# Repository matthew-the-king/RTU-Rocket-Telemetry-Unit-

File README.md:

# RTU-Rocket-Telemetry-Unit-
The RTU(Rocket Telemetry Unit) is an all-in-one solution for logging and transmitting data, plus controlling up to 3 servos. 

## Specifications
The RTU contains the following:<br>
MCU: STM32H725RGV6<br>
Barometer: BMP581<br>
IMU: BMI270<br>

For Power, the RTU has a 3.3V regulator and a 5v regulator for servos.<br>

## Recording Data
The RTU can record data to an SD card, provided that an SD card is inserted into the SD card port.<br>

## Transmitting Data
The RTU can transmit data through an on-board LoRa module; you must connect the appropriate u.fl antenna to the antenna port for the module to transmit.<br>

## Servo Control
The RTU can control up to three 5V servos; the servo ports can be found in these locations:<br>

## Production 
|Designator                                                                                      |Footprint                               |Quantity|Value                  |    Link   | Price |
|------------------------------------------------------------------------------------------------|----------------------------------------|--------|-----------------------|-----------|-------|
|C10, C12, C19, C28, C36, C40                                                                    |0603                                    |6       |1uF                    | [Link](https://www.digikey.com/en/products/detail/kemet/C0603C105K4RACTU/2199788) | $0.83(Cheaper to buy 10) | 
|C11, C29, C30, C37, C38, C39                                                                    |0603                                    |6       |10uF                   | [Link](https://www.digikey.com/en/products/detail/murata-electronics/GRT188R61C106KE13D/5416739) | $1.75(Cheaper to buy 10)|
|C13, C14, C15, C16, C17, C18, C21, C22, C27, C3, C32, C34, C35, C4, C42, C43, C5, C6, C7, C8, C9|0402                                    |21      |0.1uF                  | [Link](https://www.digikey.com/en/products/detail/murata-electronics/GCM155R71H104KE02D/4903704) | $0.74 |
|C2, C49, C50                                                                                    |0603                                    |3       |22uF                   | [Link](https://www.digikey.com/en/products/detail/samsung-electro-mechanics/CL10A226MO7JZNC/7320581) | $2.40 |
|C20, C31, C41, C46, C47, C48                                                                    |CAP_E61_CHC                             |6       |100uF                  | [Link](https://www.digikey.com/en/products/detail/chemi-con/APXG160ARA101ME61G/3983370) | $4.26 |
|C23, C24                                                                                        |0603                                    |2       |2.2uF                  | [Link](https://www.digikey.com/en/products/detail/murata-electronics/GRM188R71A225KE15D/1033256) | $0.32 |
|C25, C26                                                                                        |0402                                    |2       |10pF                   | [Link](https://www.digikey.com/en/products/detail/murata-electronics/GRM1555C1H100FA01D/2543854) | $0.20 |
|C33                                                                                             |0603                                    |1       |4.7uF                  | [Link](https://www.digikey.com/en/products/detail/murata-electronics/GRM188R61E475KE11D/3900465) | $0.26 |
|C44                                                                                             |0603                                    |1       |4700pF                 | [Link](https://www.digikey.com/en/products/detail/murata-electronics/GRM1885C1H472JA01D/4421616) | $0.12 | 
|C45                                                                                             |0402                                    |1       |100pF                  | [Link](https://www.digikey.com/en/products/detail/murata-electronics/GRM1555C1H101GA01D/3693920) | $0.11 |
|D1                                                                                              |0805                                    |1       |LED                    | [Link](https://www.digikey.com/en/products/detail/liteon/LTST-C170GKT/269226?s=N4IgTCBcDaIDIBUDKCC0BhAjAdgAwHEBpBEAXQF8g) | $0.17 |
|FB1                                                                                             |0603                                    |1       |120R                   | [Link](https://www.digikey.com/en/products/detail/pulse-electronics/PE-0603PFB121ST/5050544) | $0.10 |
|FPWM1, PFM1, R15, R16, R6, R7                                                                   |0402                                    |6       |10kΩ                   | [Link](https://www.digikey.com/en/products/detail/yageo/RC0402JR-0710KL/726418?s=N4IgTCBcDaIEoGEAMAWJYBScC0SDsAjEgNIAyIAugL5A) | $0.21(Cheaper to buy 10) |
|J1                                                                                              |GCT_MEM2075-00-140-01-A                 |1       |MEM2075-00-140-01-A    | [Link](https://www.digikey.com/en/products/detail/gct/MEM2075-00-140-01-A/9859614) | $1.92 |
|J2                                                                                              |SAMESKY_UJ20-C-H-G-SMT-P16-TR           |1       |UJ20-C-H-G-SMT-1-P16-TR| [Link](https://www.digikey.com/en/products/detail/same-sky-formerly-cui-devices/UJ20-C-H-G-SMT-P16-TR/24818595) | $0.65 |
|J4                                                                                              |JST_B6B-XH-A                            |1       |B6B-XH-A               | [Link](https://www.digikey.com/en/products/detail/jst-sales-america-inc/B6B-XH-A/1000381) | $0.23 |
|J5                                                                                              |JST_B4B-XH-A                            |1       |B4B-XH-A               | [Link](https://www.digikey.com/en/products/detail/jst-sales-america-inc/B4B-XH-A/1651047) | $0.17 |
|L1                                                                                              |1008                                    |1       |1uH                    | [Link](https://www.digikey.com/en/products/detail/murata-electronics/DFE252012P-1R0M-P2/5247258?s=N4IgTCBcDaICIDECiYCsYAMBGMAFAtFgEoYCyAvLmAAQgC6AvkA) | $0.22 |
|L2                                                                                              |L_Wurth_WE-LHCA-1040                    |1       |4.7uH                  | [Link](https://www.digikey.com/en/products/detail/w%C3%BCrth-elektronik/784373680047/24774011) | $3.35 |
|R1, R2                                                                                          |0402                                    |2       |5.1kΩ                  | [Link](https://www.digikey.com/en/products/detail/yageo/RC0402FR-075K1L/726624?s=N4IgTCBcDaIEoGEAMAWJYBicC0SDsArANICMAMiALoC%2BQA) | $0.20 |
|R10                                                                                             |0402                                    |1       |330Ω                   | [Link](https://www.digikey.com/en/products/detail/yageo/RC0402FR-07330RL/726594) | $0.10 |
|R11, R12, R4, R5                                                                                |0402                                    |4       |4.7kΩ                  | [Link](https://www.digikey.com/en/products/detail/yageo/RC0402JR-074K7L/726477) | $0.21(Cheaper to buy 10) |
|R13                                                                                             |0402                                    |1       |27.4kΩ                 | [Link](https://www.digikey.com/en/products/detail/yageo/RC0402FR-0727K4L/2827587) | $0.10 |
|R14                                                                                             |0402                                    |1       |23.2kΩ                 | [Link](https://www.digikey.com/en/products/detail/panasonic-industry/ERJ-2RKF2322X/192235) | $0.10 |
|R3                                                                                              |0402                                    |1       |0Ω                     | [Link](https://www.digikey.com/en/products/detail/panasonic-industry/ERJ-2GE0R00X/146727) | $0.10 |
|R8                                                                                              |0603                                    |1       |511kΩ                  | [Link](https://www.digikey.com/en/products/detail/yageo/RC0603FR-07511KL/727288) | $0.10 |
|R9                                                                                              |0603                                    |1       |91kΩ                   | [Link](https://www.digikey.com/en/products/detail/yageo/RC0603JR-0791KL/726841) | $0.10 |
|U1                                                                                              |QFN-68-1EP_8x8mm_P0.4mm_EP6.4x6.4mm     |1       |STM32H725RGVx          | [Link](https://www.digikey.com/en/products/detail/stmicroelectronics/STM32H725RGV6/18085383) | $14.22 |
|U2                                                                                              |QFN10_BMP581_BOS                        |1       |BMP581                 | [Link](https://www.digikey.com/en/products/detail/bosch-sensortec/BMP581/16036134) | $3.35 |
|U3                                                                                              |XDCR_BMI270                             |1       |BMI270                 | [Link](https://www.digikey.com/en/products/detail/bosch-sensortec/BMI270/9974486) | $4.23 |
|U4                                                                                              |COMM-SMD_12P-L11.6-W11.0-P1.27_114993390|1       |WIO-SX1262_C9900174795 | [Link](https://www.digikey.com/en/products/detail/seeed-technology-co-ltd/114993390/25835823) | $5.95 |
|U5                                                                                              |PSON50P145X100X60-6N                    |1       |TPD4S012DRYR           | [Link](https://www.digikey.com/en/products/detail/texas-instruments/TPD4S012DRYR/2037539) | $1.19 |
|U6                                                                                              |VAL0015A-MFG                            |1       |XTPS55285VALR          | [Link](https://www.digikey.com/en/products/detail/texas-instruments/TPS55285VALR/28143335) | $4.15 |
|U7                                                                                              |SOT50P160X60-8N                         |1       |TPS631000DRLR          | [Link](https://www.digikey.com/en/products/detail/texas-instruments/TPS631000DRLR/15965499) | $2.20 |
|Y1                                                                                              |CRYSTAL_ABM8G_ABR                       |1       |ABM8G-25.000MHZ-B4Y-T  | [Link](https://www.digikey.com/en/products/detail/abracon-llc/ABM8G-25-000MHZ-B4Y-T/2218043) | $0.86 |
||||||Total Price:$54.96 + plus shipping ~ $5.00|

For the PCB, I recommend using JLPCB; it costs only $8 for 5 boards plus shipping. 
## Firmware
Currently, there is no firmware because I do not have the board yet.

# Important Information
To ensure that the 3.3V regulator works correctly, make sure to place only ONE of the resistors circled; it is recommended to place the FPWM resistor and not the PFM resistor.<br>

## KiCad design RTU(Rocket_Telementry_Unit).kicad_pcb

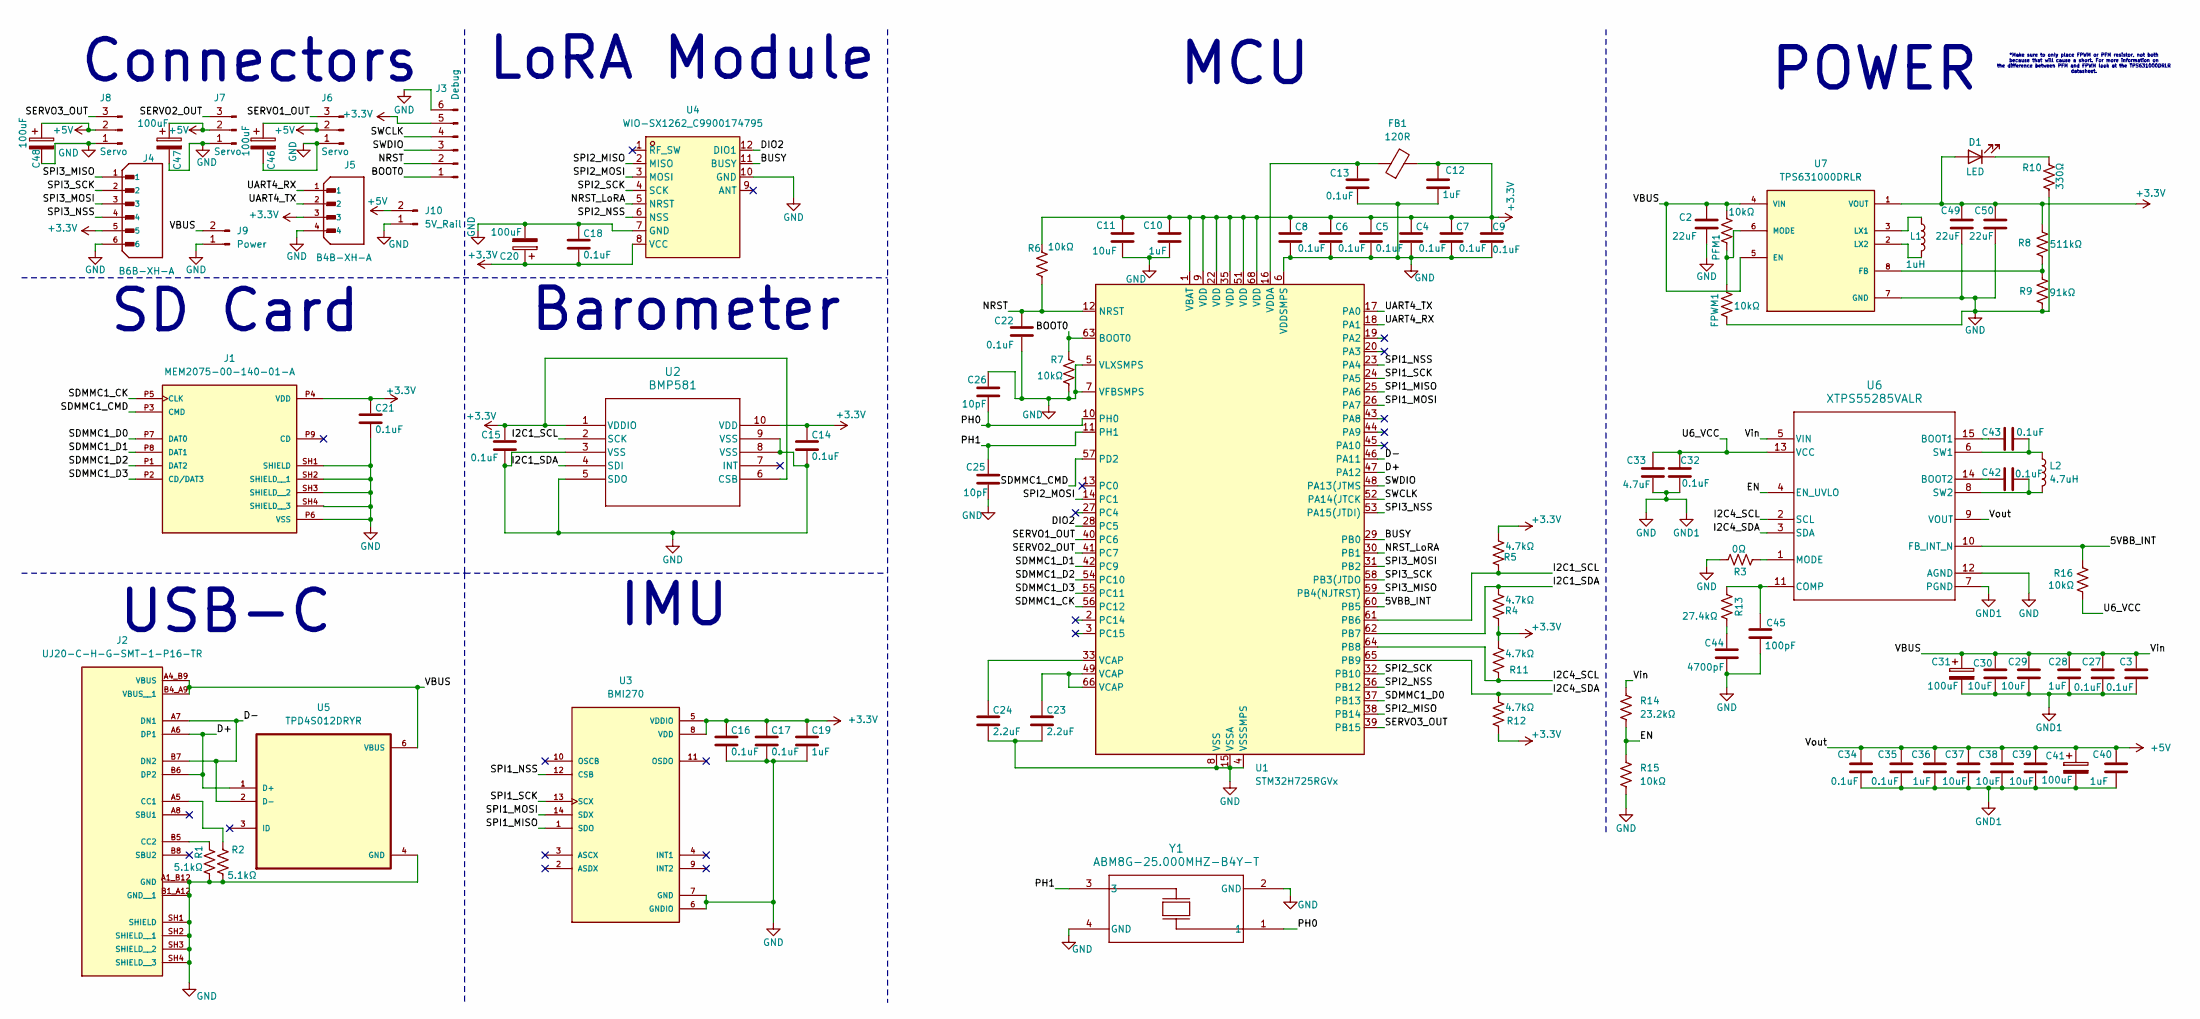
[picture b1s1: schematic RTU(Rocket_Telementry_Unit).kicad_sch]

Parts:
C2, C49, C50: 22uF; C_0603_1608Metric
C3, C4, C5, C6, C7, C8, C9, C13, C14, C15, C16, C17, C18, C21, C22, C27, C32, C34, C35, C42, C43: 0.1uF; C_0402_1005Metric
C10, C12, C19, C28, C36, C40: 1uF; C_0603_1608Metric
C11, C29, C30, C37, C38, C39: 10uF; C_0603_1608Metric
C20, C31, C41, C46, C47, C48: 100uF; CAP_E61_CHC
C23, C24: 2.2uF; C_0603_1608Metric
C25, C26: 10pF; C_0402_1005Metric
C33: 4.7uF; C_0603_1608Metric
C44: 4700pF; C_0603_1608Metric
C45: 100pF; C_0402_1005Metric
D1: LED; LED_0805_2012Metric
FB1: 120R; L_0603_1608Metric
FPWM1: 10kΩ; R_0402_1005Metric
J1: MEM2075-00-140-01-A; GCT_MEM2075-00-140-01-A; PARTREV A
J2: UJ20-C-H-G-SMT-1-P16-TR; SAMESKY_UJ20-C-H-G-SMT-P16-TR; PARTREV 1.0
J3: Debug; PinHeader_1x06_P2.54mm_Vertical
J4: B6B-XH-A; JST_B6B-XH-A; PARTREV 7/4/21
J5: B4B-XH-A; JST_B4B-XH-A; PARTREV 7/4/21
J6, J7, J8: Servo; PinHeader_1x03_P2.54mm_Vertical
J9: Power; PinHeader_1x02_P2.54mm_Vertical
J10: 5V_Rail; PinHeader_1x02_P2.54mm_Vertical
L1: 1uH; L_1008_2520Metric
L2: 4.7uH; L_Wurth_WE-LHCA-1040
PFM1: 10kΩ; R_0402_1005Metric
R1, R2: 5.1kΩ; R_0402_1005Metric
R3: 0Ω; R_0402_1005Metric
R4, R5, R11, R12: 4.7kΩ; R_0402_1005Metric
R6, R7, R15, R16: 10kΩ; R_0402_1005Metric
R8: 511kΩ; R_0603_1608Metric
R9: 91kΩ; R_0603_1608Metric
R10: 330Ω; R_0402_1005Metric
R13: 27.4kΩ; R_0402_1005Metric
R14: 23.2kΩ; R_0402_1005Metric
U1: STM32H725RGVx; QFN-68-1EP_8x8mm_P0.4mm_EP6.4x6.4mm
U2: BMP581; QFN10_BMP581_BOS
U3: BMI270; XDCR_BMI270
U4: WIO-SX1262_C9900174795; COMM-SMD_12P-L11.6-W11.0-P1.27_114993390; MPN Wio-SX1262; LCSC Part C9900174795
U5: TPD4S012DRYR; PSON50P145X100X60-6N
U6: XTPS55285VALR; VAL0015A-MFG
U7: TPS631000DRLR; SOT50P160X60-8N; PARTREV B
Y1: ABM8G-25.000MHZ-B4Y-T; CRYSTAL_ABM8G_ABR

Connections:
+3.3V: C4.1, C5.1, C6.1, C7.1, C8.1, C9.1, C10.1, C11.1, C12.1, C14.1, C15.1, C16.1, C17.1, C18.2, C19.1, C20.1, C21.1, C49.1, C50.1, D1.2 (A), FB1.2, J1.P4 (VDD), J3.5, J4.5, J5.3, R4.1, R5.2, R6.1, R8.2, R11.2, R12.1, U1.1 (VBAT), U1.9 (VDD), U1.22 (VDD), U1.35 (VDD), U1.51 (VDD), U1.68 (VDD), U2.1 (VDDIO), U2.6 (CSB), U2.10 (VDD), U3.5 (VDDIO), U3.8 (VDD), U4.8 (VCC), U7.1 (VOUT)
+5V: C34.1, C35.1, C36.1, C37.1, C38.1, C39.1, C40.1, C41.1, C46.1, C47.1, C48.1, J6.2, J7.2, J8.2, J10.2, U6.9 (VOUT)
/5VBB_INT: R16.1, U1.60 (PB5), U6.10 (FB_INT_N)
/BOOT0: J3.1, R7.1, U1.63 (BOOT0)
/BUSY: U1.29 (PB0), U4.11 (BUSY)
/D+: J2.A6 (DP1), J2.B6 (DP2), U1.47 (PA12), U5.1 (D+)
/D-: J2.A7 (DN1), J2.B7 (DN2), U1.46 (PA11), U5.2 (D-)
/DIO2: U1.28 (PC5), U4.12 (DIO1)
/EN: R14.2, R15.1, U6.4 (EN_UVLO)
/I2C1_SCL: R5.1, U1.61 (PB6), U2.2 (SCK)
/I2C1_SDA: R4.2, U1.62 (PB7), U2.4 (SDI)
/I2C4_SCL: R11.1, U1.64 (PB8), U6.2 (SCL)
/I2C4_SDA: R12.2, U1.65 (PB9), U6.3 (SDA)
/NRST: C22.1, J3.2, R6.2, U1.12 (NRST)
/NRST_LoRA: U1.30 (PB1), U4.5 (NRST)
/PH0: C26.2, U1.10 (PH0), Y1.1
/PH1: C25.1, U1.11 (PH1), Y1.3
/SDMMC1_CK: J1.P5 (CLK), U1.56 (PC12)
/SDMMC1_CMD: J1.P3 (CMD), U1.57 (PD2)
/SDMMC1_D0: J1.P7 (DAT0), U1.37 (PB13)
/SDMMC1_D1: J1.P8 (DAT1), U1.42 (PC9)
/SDMMC1_D2: J1.P1 (DAT2), U1.54 (PC10)
/SDMMC1_D3: J1.P2 (CD/DAT3), U1.55 (PC11)
/SERVO1_OUT: J6.3, U1.40 (PC6)
/SERVO2_OUT: J7.3, U1.41 (PC7)
/SERVO3_OUT: J8.3, U1.39 (PB15)
/SPI1_MISO: U1.25 (PA6), U3.1 (SDO)
/SPI1_MOSI: U1.26 (PA7), U3.14 (SDX)
/SPI1_NSS: U1.23 (PA4), U3.12 (CSB)
/SPI1_SCK: U1.24 (PA5), U3.13 (SCX)
/SPI2_MISO: U1.38 (PB14), U4.2 (MISO)
/SPI2_MOSI: U1.14 (PC1), U4.3 (MOSI)
/SPI2_NSS: U1.36 (PB12), U4.6 (NSS)
/SPI2_SCK: U1.32 (PB10), U4.4 (SCK)
/SPI3_MISO: J4.1, U1.59 (PB4(NJTRST))
/SPI3_MOSI: J4.3, U1.31 (PB2)
/SPI3_NSS: J4.4, U1.53 (PA15(JTDI))
/SPI3_SCK: J4.2, U1.58 (PB3(JTDO)
/SWCLK: J3.4, U1.52 (PA14(JTCK)
/SWDIO: J3.3, U1.48 (PA13(JTMS)
/U6_VCC: C32.1, C33.1, R16.2, U6.13 (VCC)
/UART4_RX: J5.1, U1.18 (PA1)
/UART4_TX: J5.2, U1.17 (PA0)
/VBUS: C2.1, C3.1, C27.1, C28.1, C29.1, C30.1, C31.1, J2.A4_B9 (VBUS), J2.A9_B4, J2.B4_A9 (VBUS__1), J9.2, PFM1.2, R14.1, U5.6 (VBUS), U6.5 (VIN), U7.4 (VIN), U7.5 (EN)
GND: C2.2, C3.2, C4.2, C5.2, C6.2, C7.2, C8.2, C9.2, C10.2, C11.2, C12.2, C13.2, C14.2, C15.2, C16.2, C17.2, C18.1, C19.2, C20.2, C21.2, C22.2, C23.2, C24.2, C25.2, C26.1, C27.2, C28.2, C29.2, C30.2, C31.2, C32.2, C33.2, C34.2, C35.2, C36.2, C37.2, C38.2, C39.2, C40.2, C41.2, C44.2, C45.2, C46.2, C47.2, C48.2, C49.2, C50.2, FPWM1.1, J1.P6 (VSS), J1.SH1 (SHIELD), J1.SH2 (SHIELD__1), J1.SH3 (SHIELD__2), J1.SH4 (SHIELD__3), J2.A1_B12 (GND), J2.A12_B1, J2.B1_A12 (GND__1), J2.SH1 (SHIELD), J2.SH2 (SHIELD__1), J2.SH3 (SHIELD__2), J2.SH4 (SHIELD__3), J3.6, J4.6, J5.4, J6.1, J7.1, J8.1, J9.1, J10.1, R1.2, R2.2, R3.2, R7.2, R9.1, R10.1, R15.2, U1.4 (VSSSMPS), U1.5 (VLXSMPS), U1.6 (VDDSMPS), U1.7 (VFBSMPS), U1.8 (VSS), U1.15 (VSSA), U1.21 (VSS), U1.34 (VSS), U1.50 (VSS), U1.67 (VSS), U1.69 (VSS), U2.3 (VSS), U2.5 (SDO), U2.8 (VSS), U2.9 (VSS), U3.6 (GNDIO), U3.7 (GND), U4.7 (GND), U4.10 (GND), U5.4 (GND), U6.7 (PGND), U6.12 (AGND), U7.7 (GND), Y1.2 (GND), Y1.4 (GND)
unnamed: C23.1, U1.49 (VCAP), U1.66 (VCAP)
unnamed: C24.1, U1.33 (VCAP)
unnamed: C44.1, R13.2
unnamed: D1.1 (K), R10.2
unnamed: J2.A5 (CC1), R2.1
unnamed: J2.B5 (CC2), R1.1
unnamed: C13.1, FB1.1, U1.16 (VDDA)
unnamed: C43.1, U6.15 (BOOT1)
unnamed: C42.1, U6.14 (BOOT2)
unnamed: C45.1, R13.1, U6.11 (COMP)
unnamed: R3.1, U6.1 (MODE)
unnamed: C43.2, L2.1, U6.6 (SW1)
unnamed: C42.2, L2.2, U6.8 (SW2)
unnamed: R8.1, R9.2, U7.8 (FB)
unnamed: L1.1, U7.3 (LX1)
unnamed: L1.2, U7.2 (LX2)
unnamed: FPWM1.2, PFM1.1, U7.6 (MODE)

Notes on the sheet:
POWER
MCU
LoRA Module
Connectors
Barometer
IMU
SD Card
USB-C
*Make sure to only place FPWM or PFM resistor, not both because that will cause a short. For more information on the difference between PFM and FPWM look at the TPS631000DRLR datasheet.

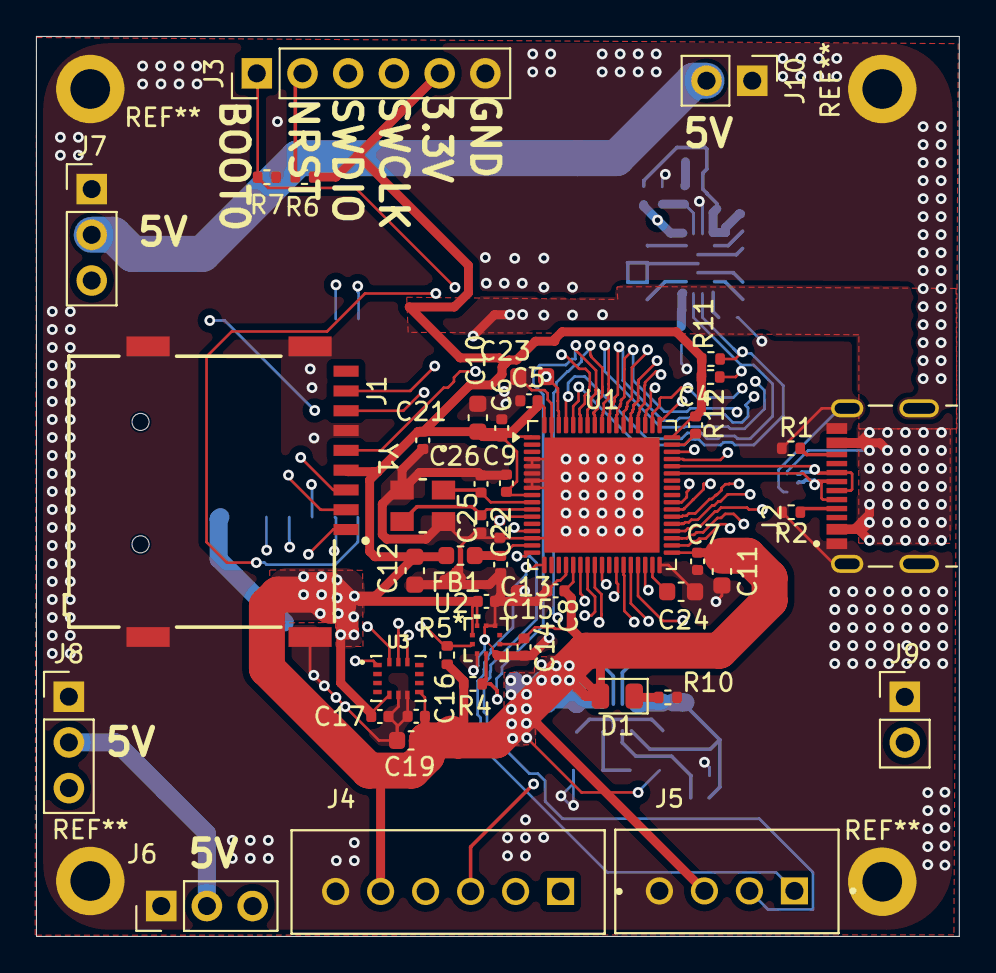
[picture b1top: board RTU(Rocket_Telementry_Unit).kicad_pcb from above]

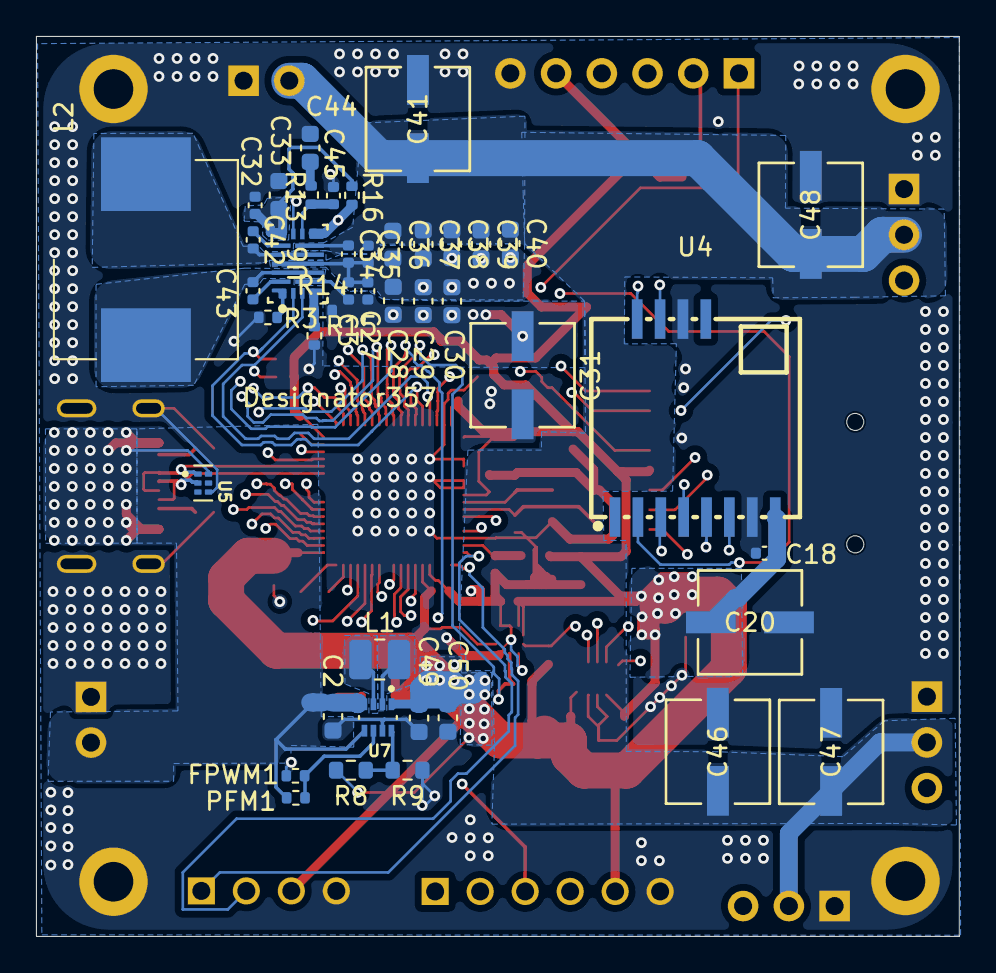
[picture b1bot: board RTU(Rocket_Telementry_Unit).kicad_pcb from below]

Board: 4 copper layers, 51.3 x 50.0 mm, 89 parts (43 on the bottom side), 62 nets.

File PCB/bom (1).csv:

Designator,Footprint,Quantity,Value,LCSC Part #
"C10, C12, C19, C28, C36, C40",0603,6,1uF,
"C11, C29, C30, C37, C38, C39",0603,6,10uF,
"C13, C14, C15, C16, C17, C18, C21, C22, C27, C3, C32, C34, C35, C4, C42, C43, C5, C6, C7, C8, C9",0402,21,0.1uF,
"C2, C49, C50",0603,3,22uF,
"C20, C31, C41, C46, C47, C48",CAP_E61_CHC,6,100uF,
"C23, C24",0603,2,2.2uF,
"C25, C26",0402,2,10pF,
C33,0603,1,4.7uF,
C44,0603,1,4700pF,
C45,0402,1,100pF,
D1,0805,1,LED,
FB1,0603,1,120R,
"FPWM1, PFM1, R15, R16, R6, R7",0402,6,10kΩ,
J1,GCT_MEM2075-00-140-01-A,1,MEM2075-00-140-01-A,
J10,PinHeader_1x02_P2.54mm_Vertical,1,5V_Rail,
J2,SAMESKY_UJ20-C-H-G-SMT-P16-TR,1,UJ20-C-H-G-SMT-1-P16-TR,
J3,PinHeader_1x06_P2.54mm_Vertical,1,Debug,
J4,JST_B6B-XH-A,1,B6B-XH-A,
J5,JST_B4B-XH-A,1,B4B-XH-A,
"J6, J7, J8",PinHeader_1x03_P2.54mm_Vertical,3,Servo,
J9,PinHeader_1x02_P2.54mm_Vertical,1,Power,
L1,1008,1,1uH,
L2,L_Wurth_WE-LHCA-1040,1,4.7uH,
"R1, R2",0402,2,5.1kΩ,
R10,0402,1,330Ω,
"R11, R12, R4, R5",0402,4,4.7kΩ,
R13,0402,1,27.4kΩ,
R14,0402,1,23.2kΩ,
R3,0402,1,0Ω,
R8,0603,1,511kΩ,
R9,0603,1,91kΩ,
U1,QFN-68-1EP_8x8mm_P0.4mm_EP6.4x6.4mm,1,STM32H725RGVx,
U2,QFN10_BMP581_BOS,1,BMP581,
U3,XDCR_BMI270,1,BMI270,
U4,COMM-SMD_12P-L11.6-W11.0-P1.27_114993390,1,WIO-SX1262_C9900174795,C9900174795
U5,PSON50P145X100X60-6N,1,TPD4S012DRYR,
U6,VAL0015A-MFG,1,XTPS55285VALR,
U7,SOT50P160X60-8N,1,TPS631000DRLR,
Y1,CRYSTAL_ABM8G_ABR,1,ABM8G-25.000MHZ-B4Y-T,
